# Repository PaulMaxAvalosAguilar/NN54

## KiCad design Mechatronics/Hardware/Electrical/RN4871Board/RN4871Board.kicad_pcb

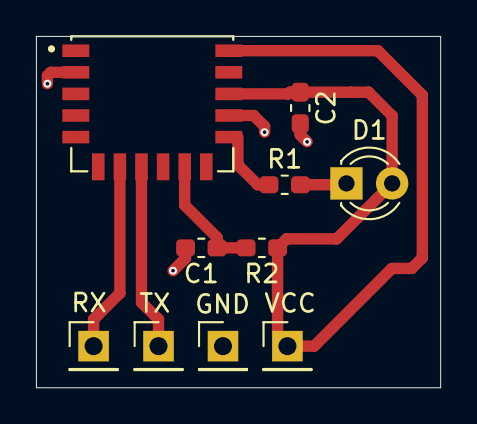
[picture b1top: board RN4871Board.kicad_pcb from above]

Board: 2 copper layers, 22.5 x 19.5 mm, 10 parts (0 on the bottom side), 7 nets.

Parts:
C1: 1uF; C_0603_1608Metric_Pad1.05x0.95mm_HandSolder
C2: 10uF; C_0603_1608Metric_Pad1.05x0.95mm_HandSolder
D1: LED; LED_D3.0mm
J1, J2, J3, J4: Conn_01x01_Male; PinHeader_1x01_P2.54mm_Vertical
R1: 330; R_0603_1608Metric_Pad1.05x0.95mm_HandSolder
R2: 10K; R_0603_1608Metric_Pad1.05x0.95mm_HandSolder
U1: RN4871; Bluetooth_Module_RN4871

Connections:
+3V3: C2.1, D1.2, J4.1, R2.1, U1.14, U1.16
GND: C1.2, C2.2, J1.1, U1.2, U1.13
unnamed: C1.1, R2.2, U1.10
unnamed: D1.1, R1.2
unnamed: J2.1, U1.7
unnamed: J3.1, U1.8
unnamed: R1.1, U1.12
